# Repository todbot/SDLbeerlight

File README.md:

# SDLbeerlight

An overly complicated light for announcing a certain time of day (or state of mind).  Created by 0x02 Design Lab Residents.

The Beer Light consists of:

- Arduino Uno running sketch in this repo
- Custom Arduino shield acting as breakout board for the following modules:
- An illuminated big button with integrated LED
- 24 WS2812 RGB LEDs
- Sure Electronics DE-DP14211 LED panel http://store3.sure-electronics.com/de-dp14211
- MP3 module with built-in 10W amp FN-BC04-TB -  https://electronics123.odoo.com/shop/product/fn-bc04-tb-4-buttons-triggered-mp3-player-board-with-10w-amplifier-and-terminal-blocks-8267 and two speakers
- LM2596 adjustable power supply module set to +5V output
- Custom-designed box and graphics by MotherFather Design

Dan, if you want to change things:
- The file "001.mp3" on the MP3 SD card is the sound that is played
- The trimpot on the MP3 board controls the sound volume
- The variable "msg" in the sketch sets the sign's default text message

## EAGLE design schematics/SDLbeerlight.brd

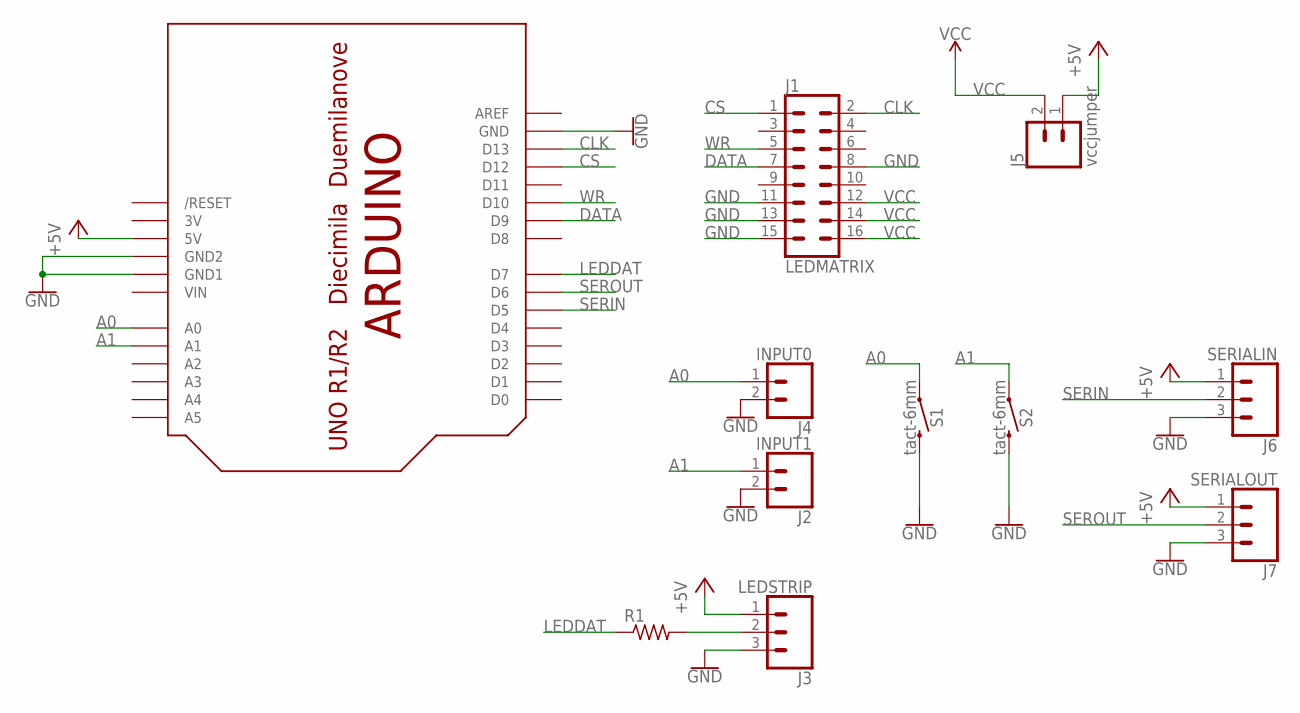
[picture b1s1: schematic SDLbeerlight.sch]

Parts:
J1: LEDMATRIX; 2X8
J2: INPUT1; 1X02_LONGPADS
J3: LEDSTRIP; 1X03_LONGPADS
J4: INPUT0; 1X02_LONGPADS
J5: vccjumper; 1X02_LOCK_LONGPADS
J6: SERIALIN; 1X03_LONGPADS
J7: SERIALOUT; 1X03_LONGPADS
R1: R-US_0204/7; 0204/7
S1, S2: tact-6mm; TACTILE_SWITCH_PTH_6.0MM
U$2: ARDUINOUNO; ARDUINO

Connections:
3V: U$2.3V
+5V: J3.1, J5.1, J6.1, J7.1, U$2.5V
A0: J4.1, S1.1, U$2.A0
A1: J2.1, S2.1, U$2.A1
CLK: J1.2, U$2.D13
CS: J1.1, U$2.D12
DATA: J1.7, U$2.D9
GND: J1.8, J1.11, J1.13, J1.15, J2.2, J3.3, J4.2, J6.3, J7.3, S1.3 (2), S2.3 (2), U$2.GND, U$2.GND1, U$2.GND2
LEDDAT: R1.1, U$2.D7
unnamed: J3.2, R1.2
SERIN: J6.2, U$2.D5
SEROUT: J7.2, U$2.D6
VCC: J1.12, J1.14, J1.16, J5.2
VIN: U$2.VIN
WR: J1.5, U$2.D10

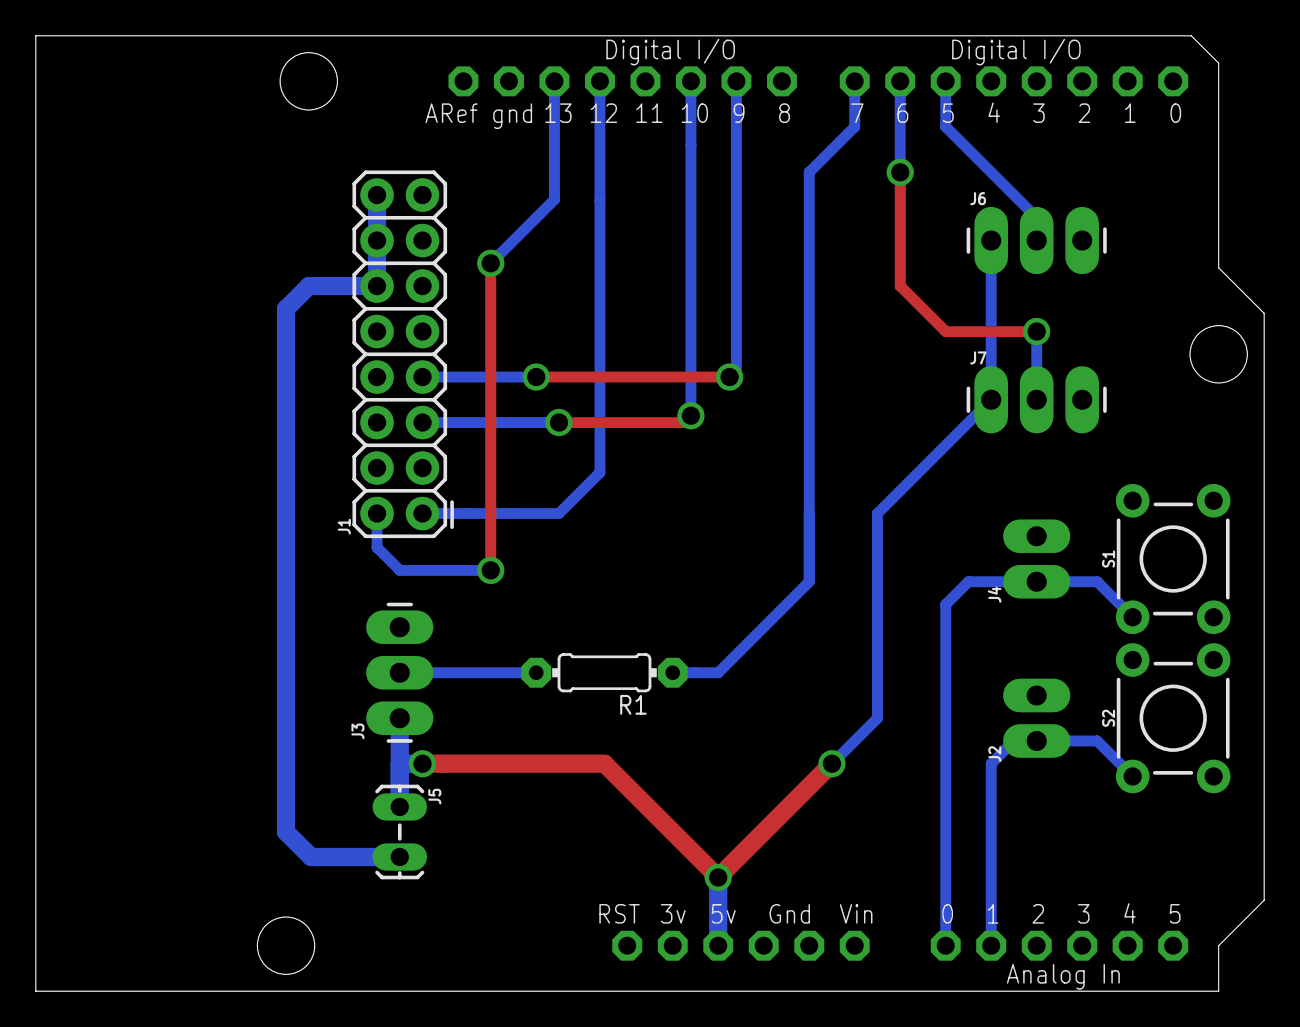
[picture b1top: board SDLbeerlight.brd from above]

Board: 2 copper layers, 68.6 x 53.3 mm, 11 parts (0 on the bottom side), 13 nets.

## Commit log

2017-06-19 added libzips
2017-06-19 added attribution
2017-06-22 code actually does something useful now
2017-06-23 small update, and doc about libraries
2017-06-23 fixed bluetooth dropping chars issue (sorta) because of fastled being called too often
2017-06-24 added docs
2017-06-24 added more docs
2017-06-24 fix firmware so sound turns off
2017-06-24 added pics
2017-06-26 updated docs
2017-06-26 added alberto
2017-06-27 SDLbeerlight Design Files
    Adobe Illustrator files you can use to cut out your own Beerlight!

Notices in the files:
parts and their libraries:
SparkFun-Connectors: Licensing: Creative Commons ShareAlike 4.0 International - https://creativecommons.org/licenses/by-sa/4.0
